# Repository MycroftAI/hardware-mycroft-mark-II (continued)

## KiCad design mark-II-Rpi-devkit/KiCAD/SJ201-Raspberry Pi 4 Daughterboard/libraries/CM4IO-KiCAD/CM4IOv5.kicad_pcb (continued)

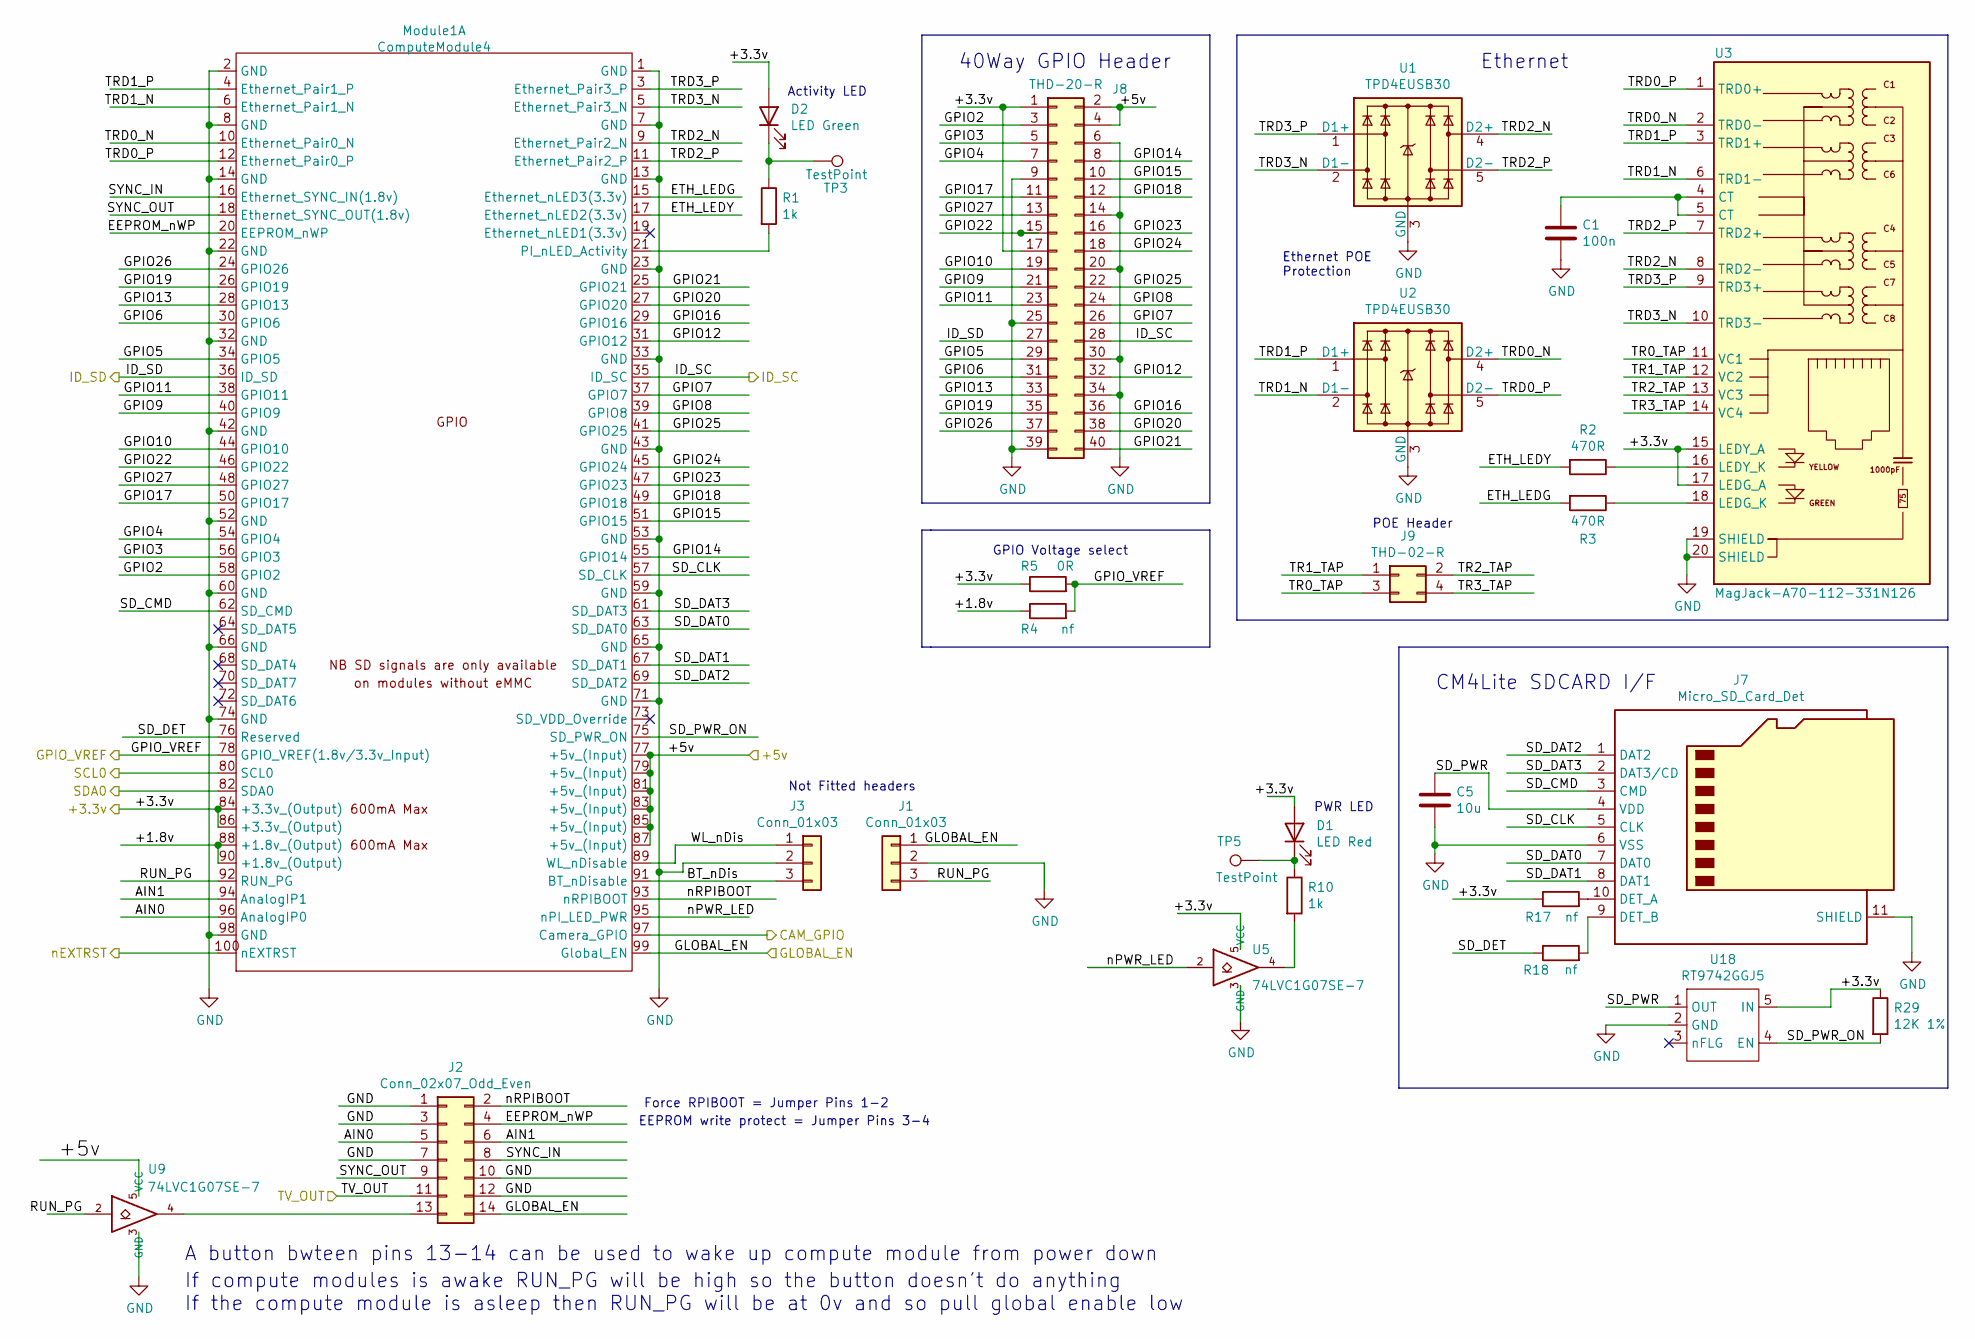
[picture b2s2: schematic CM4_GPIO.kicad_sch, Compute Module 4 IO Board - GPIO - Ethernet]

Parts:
C1: 100n; C_0402_1005Metric; Part Description 0.1uF 10% 16V Ceramic Capacitor X7R 040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
C5: 10u; C_0805_2012Metric; Part Description 10uF 10% 10V Ceramic Capacitor X7R 0805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
D1: LED Red; LED_0603_1608Metric; Part Description Red 620nm LED Indication - Discrete 2.2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
D2: LED Green; LED_0603_1608Metric; Part Description Green 572nm LED Indication - Discrete 2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
J1, J3: Conn_01x03; PinHeader_1x03_P2.54mm_Vertical; Part Description 3pin 0.1" connector
J2: Conn_02x07_Odd_Even; PinHeader_2x07_P2.54mm_Vertical; Part Description PinHeader_2x07_P2.54mm_Vertical
J7: Micro_SD_Card_Det; SDCARD_MOLEX_503398-1892; Part Description 9 (8 + 1) Position Card Connector micro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
J8: THD-20-R; PinHeader_2x20_P2.54mm_Vertical; Part Description PinHeader_2x20_P2.54mm_Vertical
J9: THD-02-R; PinHeader_2x02_P2.54mm_Vertical; Part Description PinHeader_2x02_P2.54mm_Vertical
Module1: ComputeModule4; Raspberry-Pi-4-Compute-Module; Part Description 100 Position Connector Receptacle, Cent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
R1, R10: 1k; R_0402_1005Metric; Part Description Resistor 1K M1005 1% 63mW
R2, R3: 470R; R_0402_1005Metric; Part Description Resistor 470R M1005 1% 63mW
R4: nf; R_0805_2012Metric_Pad1.15x1.40mm_HandSolder
R5: 0R; R_0805_2012Metric_Pad1.15x1.40mm_HandSolder; Part Description Resistor 0R M2012 5%
R17, R18: nf; R_0402_1005Metric; Part Description Resistor 1K M1005 1% 63mW
R29: 12K 1%; R_0402_1005Metric; Part Description Resistor 12K M1005 1% 63mW
TP3, TP5: TestPoint; TestPoint_Pad_2.0x2.0mm
U1, U2: TPD4EUSB30; USON-10_2.5x1.0mm_P0.5mm; Part Description Quad TVS diode for high speed signals (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
U3: MagJack-A70-112-331N126; TRJG0926HENL; Part Description Gigabit Ethernet Magjack
U5, U9: 74LVC1G07SE-7; SOT-353_SC-70-5; Part Description Buffer, Non-Inverting 1 Element 1 Bit p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
U18: RT9742GGJ5; SOT-23-5; Part Description Power Switch/Driver 1:1 N-Channel 1A TS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

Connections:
/+3.3v: D1.2 (A), D2.2 (A), J8.1, J8.17, Module1.84 (+3.3v_(Output)), Module1.86 (+3.3v_(Output)), R5.1, R17.1, R29.1, U3.15 (LEDY_A), U3.17 (LEDG_A), U5.5 (VCC), U18.5 (IN); also elsewhere on the board
/+5v: J8.2, J8.4, Module1.77 (+5v_(Input)), Module1.79 (+5v_(Input)), Module1.81 (+5v_(Input)), Module1.83 (+5v_(Input)), Module1.85 (+5v_(Input)), Module1.87 (+5v_(Input)), U9.5 (VCC); also elsewhere on the board
/CAM_GPIO: Module1.97 (Camera_GPIO); also elsewhere on the board
/CM4_GPIO ( Ethernet, GPIO, SDCARD)/+1.8v: Module1.88 (+1.8v_(Output)), Module1.90 (+1.8v_(Output)), R4.1
/CM4_GPIO ( Ethernet, GPIO, SDCARD)/AIN0: J2.5, Module1.96 (AnalogIP0)
/CM4_GPIO ( Ethernet, GPIO, SDCARD)/AIN1: J2.6, Module1.94 (AnalogIP1)
/CM4_GPIO ( Ethernet, GPIO, SDCARD)/BT_nDis: J3.3, Module1.91 (BT_nDisable)
/CM4_GPIO ( Ethernet, GPIO, SDCARD)/EEPROM_nWP: J2.4, Module1.20 (EEPROM_nWP)
/CM4_GPIO ( Ethernet, GPIO, SDCARD)/ETH_LEDG: Module1.15 (Ethernet_nLED3(3.3v)), R3.2
/CM4_GPIO ( Ethernet, GPIO, SDCARD)/ETH_LEDY: Module1.17 (Ethernet_nLED2(3.3v)), R2.2
/CM4_GPIO ( Ethernet, GPIO, SDCARD)/GPIO2: J8.3, Module1.58 (GPIO2)
/CM4_GPIO ( Ethernet, GPIO, SDCARD)/GPIO3: J8.5, Module1.56 (GPIO3)
/CM4_GPIO ( Ethernet, GPIO, SDCARD)/GPIO4: J8.7, Module1.54 (GPIO4)
/CM4_GPIO ( Ethernet, GPIO, SDCARD)/GPIO5: J8.29, Module1.34 (GPIO5)
/CM4_GPIO ( Ethernet, GPIO, SDCARD)/GPIO6: J8.31, Module1.30 (GPIO6)
/CM4_GPIO ( Ethernet, GPIO, SDCARD)/GPIO7: J8.26, Module1.37 (GPIO7)
/CM4_GPIO ( Ethernet, GPIO, SDCARD)/GPIO8: J8.24, Module1.39 (GPIO8)
/CM4_GPIO ( Ethernet, GPIO, SDCARD)/GPIO9: J8.21, Module1.40 (GPIO9)
/CM4_GPIO ( Ethernet, GPIO, SDCARD)/GPIO10: J8.19, Module1.44 (GPIO10)
/CM4_GPIO ( Ethernet, GPIO, SDCARD)/GPIO11: J8.23, Module1.38 (GPIO11)
/CM4_GPIO ( Ethernet, GPIO, SDCARD)/GPIO12: J8.32, Module1.31 (GPIO12)
/CM4_GPIO ( Ethernet, GPIO, SDCARD)/GPIO13: J8.33, Module1.28 (GPIO13)
/CM4_GPIO ( Ethernet, GPIO, SDCARD)/GPIO14: J8.8, Module1.55 (GPIO14)
/CM4_GPIO ( Ethernet, GPIO, SDCARD)/GPIO15: J8.10, Module1.51 (GPIO15)
/CM4_GPIO ( Ethernet, GPIO, SDCARD)/GPIO16: J8.36, Module1.29 (GPIO16)
/CM4_GPIO ( Ethernet, GPIO, SDCARD)/GPIO17: J8.11, Module1.50 (GPIO17)
/CM4_GPIO ( Ethernet, GPIO, SDCARD)/GPIO18: J8.12, Module1.49 (GPIO18)
/CM4_GPIO ( Ethernet, GPIO, SDCARD)/GPIO19: J8.35, Module1.26 (GPIO19)
/CM4_GPIO ( Ethernet, GPIO, SDCARD)/GPIO20: J8.38, Module1.27 (GPIO20)
/CM4_GPIO ( Ethernet, GPIO, SDCARD)/GPIO21: J8.40, Module1.25 (GPIO21)
/CM4_GPIO ( Ethernet, GPIO, SDCARD)/GPIO22: J8.15, Module1.46 (GPIO22)
/CM4_GPIO ( Ethernet, GPIO, SDCARD)/GPIO23: J8.16, Module1.47 (GPIO23)
/CM4_GPIO ( Ethernet, GPIO, SDCARD)/GPIO24: J8.18, Module1.45 (GPIO24)
/CM4_GPIO ( Ethernet, GPIO, SDCARD)/GPIO25: J8.22, Module1.41 (GPIO25)
/CM4_GPIO ( Ethernet, GPIO, SDCARD)/GPIO26: J8.37, Module1.24 (GPIO26)
/CM4_GPIO ( Ethernet, GPIO, SDCARD)/GPIO27: J8.13, Module1.48 (GPIO27)
/CM4_GPIO ( Ethernet, GPIO, SDCARD)/RUN_PG: J1.3, Module1.92 (RUN_PG), U9.2
/CM4_GPIO ( Ethernet, GPIO, SDCARD)/SD_CLK: J7.5 (CLK), Module1.57 (SD_CLK)
/CM4_GPIO ( Ethernet, GPIO, SDCARD)/SD_CMD: J7.3 (CMD), Module1.62 (SD_CMD)
/CM4_GPIO ( Ethernet, GPIO, SDCARD)/SD_DAT0: J7.7 (DAT0), Module1.63 (SD_DAT0)
/CM4_GPIO ( Ethernet, GPIO, SDCARD)/SD_DAT1: J7.8 (DAT1), Module1.67 (SD_DAT1)
/CM4_GPIO ( Ethernet, GPIO, SDCARD)/SD_DAT2: J7.1 (DAT2), Module1.69 (SD_DAT2)
/CM4_GPIO ( Ethernet, GPIO, SDCARD)/SD_DAT3: J7.2 (DAT3/CD), Module1.61 (SD_DAT3)
/CM4_GPIO ( Ethernet, GPIO, SDCARD)/SD_DET: Module1.76 (Reserved), R18.1
/CM4_GPIO ( Ethernet, GPIO, SDCARD)/SD_PWR: C5.1, J7.4 (VDD), U18.1 (OUT)
/CM4_GPIO ( Ethernet, GPIO, SDCARD)/SD_PWR_ON: Module1.75 (SD_PWR_ON), R29.2, U18.4 (EN)
/CM4_GPIO ( Ethernet, GPIO, SDCARD)/SYNC_IN: J2.8, Module1.16 (Ethernet_SYNC_IN(1.8v))
/CM4_GPIO ( Ethernet, GPIO, SDCARD)/SYNC_OUT: J2.9, Module1.18 (Ethernet_SYNC_OUT(1.8v))
/CM4_GPIO ( Ethernet, GPIO, SDCARD)/TR0_TAP: J9.3, U3.11 (VC1)
/CM4_GPIO ( Ethernet, GPIO, SDCARD)/TR1_TAP: J9.1, U3.12 (VC2)
/CM4_GPIO ( Ethernet, GPIO, SDCARD)/TR2_TAP: J9.2, U3.13 (VC3)
/CM4_GPIO ( Ethernet, GPIO, SDCARD)/TR3_TAP: J9.4, U3.14 (VC4)
/CM4_GPIO ( Ethernet, GPIO, SDCARD)/TRD0_N: Module1.10 (Ethernet_Pair0_N), U2.4 (D2+), U2.7, U3.2 (TRD0-)
/CM4_GPIO ( Ethernet, GPIO, SDCARD)/TRD0_P: Module1.12 (Ethernet_Pair0_P), U2.5 (D2-), U2.6, U3.1 (TRD0+)
/CM4_GPIO ( Ethernet, GPIO, SDCARD)/TRD1_N: Module1.6 (Ethernet_Pair1_N), U2.2 (D1-), U2.9, U3.6 (TRD1-)
/CM4_GPIO ( Ethernet, GPIO, SDCARD)/TRD1_P: Module1.4 (Ethernet_Pair1_P), U2.1 (D1+), U2.10, U3.3 (TRD1+)
/CM4_GPIO ( Ethernet, GPIO, SDCARD)/TRD2_N: Module1.9 (Ethernet_Pair2_N), U1.4 (D2+), U1.7, U3.8 (TRD2-)
/CM4_GPIO ( Ethernet, GPIO, SDCARD)/TRD2_P: Module1.11 (Ethernet_Pair2_P), U1.5 (D2-), U1.6, U3.7 (TRD2+)
/CM4_GPIO ( Ethernet, GPIO, SDCARD)/TRD3_N: Module1.5 (Ethernet_Pair3_N), U1.2 (D1-), U1.9, U3.10 (TRD3-)
/CM4_GPIO ( Ethernet, GPIO, SDCARD)/TRD3_P: Module1.3 (Ethernet_Pair3_P), U1.1 (D1+), U1.10, U3.9 (TRD3+)
/CM4_GPIO ( Ethernet, GPIO, SDCARD)/WL_nDis: J3.1, Module1.89 (WL_nDisable)
/CM4_GPIO ( Ethernet, GPIO, SDCARD)/nPWR_LED: Module1.95 (nPI_LED_PWR), U5.2
/CM4_GPIO ( Ethernet, GPIO, SDCARD)/nRPIBOOT: J2.2, Module1.93 (nRPIBOOT)
/GLOBAL_EN: J1.1, J2.14, Module1.99 (Global_EN); also elsewhere on the board
/GPIO_VREF: Module1.78 (GPIO_VREF(1.8v/3.3v_Input)), R4.2, R5.2; also elsewhere on the board
/ID_SC: J8.28, Module1.35 (ID_SC); also elsewhere on the board
/ID_SD: J8.27, Module1.36 (ID_SD); also elsewhere on the board
/SCL0: Module1.80 (SCL0); also elsewhere on the board
/SDA0: Module1.82 (SDA0); also elsewhere on the board
/TV_OUT: J2.11; also elsewhere on the board
/nEXTRST: Module1.100 (nEXTRST); also elsewhere on the board
GND: C1.2, C5.2, J1.2, J2.1, J2.3, J2.7, J2.10, J2.12, J3.2, J7.6 (VSS), J7.11 (SHIELD), J8.6, J8.9, J8.14, J8.20, J8.25, J8.30, J8.34, J8.39, Module1.1 (GND), Module1.2 (GND), Module1.7 (GND), Module1.8 (GND), Module1.13 (GND), Module1.14 (GND), Module1.22 (GND), Module1.23 (GND), Module1.32 (GND), Module1.33 (GND), Module1.42 (GND), Module1.43 (GND), Module1.52 (GND), Module1.53 (GND), Module1.59 (GND), Module1.60 (GND), Module1.65 (GND), Module1.66 (GND), Module1.71 (GND), Module1.74 (GND), Module1.98 (GND), U1.3 (GND), U1.8 (GND), U2.3 (GND), U2.8 (GND), U3.19 (SHIELD), U3.20 (SHIELD), U5.3 (GND), U9.3 (GND), U18.2 (GND); also elsewhere on the board
unnamed: C1.1, U3.4 (CT), U3.5 (CT)
unnamed: D1.1 (K), R10.1, TP5.1
unnamed: D2.1 (K), R1.1, TP3.1
unnamed: J2.13, U9.4
unnamed: J7.9 (DET_B), R18.2
unnamed: J7.10 (DET_A), R17.2
unnamed: Module1.21 (PI_nLED_Activity), R1.2
unnamed: R2.1, U3.16 (LEDY_K)
unnamed: R3.1, U3.18 (LEDG_K)
unnamed: R10.2, U5.4

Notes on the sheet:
A button bwteen pins 13-14 can be used to wake up compute module from power down
If compute modules is awake RUN_PG will be high so the button doesn't do anything If the compute module is asleep then RUN_PG will be at 0v and so pull global enable low
Activity LED
Force RPIBOOT = Jumper Pins 1-2
Not Fitted headers
EEPROM write protect = Jumper Pins 3-4
40Way GPIO Header
GPIO Voltage select
Ethernet POE Protection
PWR LED
POE Header
CM4Lite SDCARD I/F
Ethernet

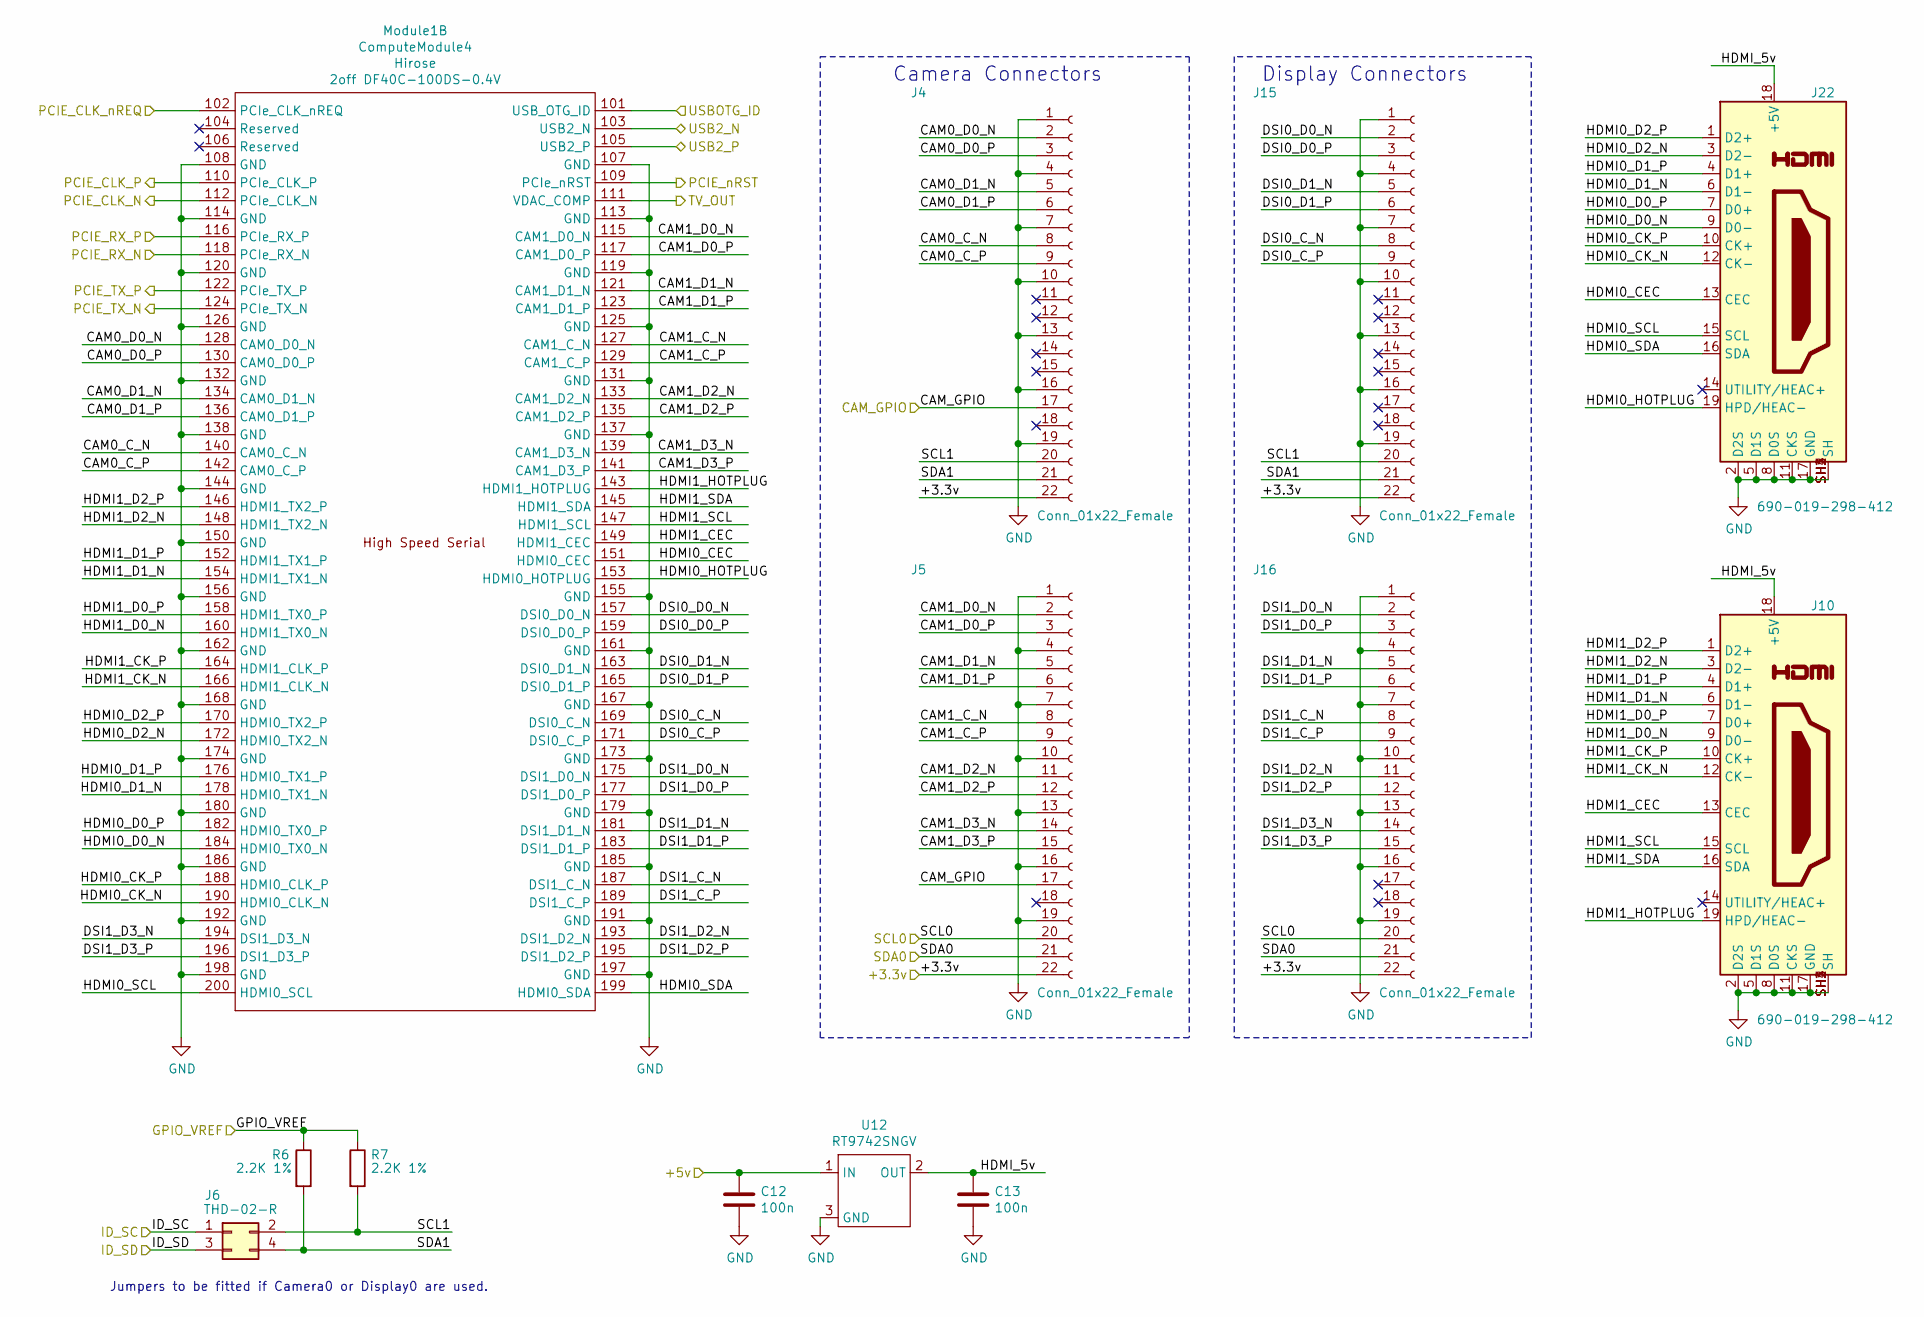
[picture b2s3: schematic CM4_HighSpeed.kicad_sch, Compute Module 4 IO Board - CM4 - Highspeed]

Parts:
C12, C13: 100n; C_0402_1005Metric; Part Description 0.1uF 10% 16V Ceramic Capacitor X7R 040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
J4, J5, J15, J16: Conn_01x22_Female; Hirose_FH12-22S-0.5SH_1x22-1MP_P0.50mm_Horizontal; Part Description 22 Position FFC, FPC Connector Contacts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
J6: THD-02-R; PinHeader_2x02_P2.54mm_Vertical; Part Description PinHeader_2x02_P2.54mm_Vertical
J10, J22: 690-019-298-412; EDAC 690-019-298-412; Part Description HDMI Connector, Right Angle, 19 Contact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
Module1: ComputeModule4; Raspberry-Pi-4-Compute-Module; Part Description 100 Position Connector Receptacle, Cent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
R6, R7: 2.2K 1%; R_0402_1005Metric; Part Description Resistor 2.2K M1005 1% 63mW
U12: RT9742SNGV; SOT-23; Part Description Power Switch/Driver 1:1 N-Channel 500mA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

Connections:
/+3.3v: J4.22, J5.22, J15.22, J16.22; also elsewhere on the board
/+5v: C12.1, U12.1 (IN); also elsewhere on the board
/CAM_GPIO: J4.17, J5.17; also elsewhere on the board
/CM4_HighSpeed/CAM0_C_N: J4.8, Module1.140 (CAM0_C_N)
/CM4_HighSpeed/CAM0_C_P: J4.9, Module1.142 (CAM0_C_P)
/CM4_HighSpeed/CAM0_D0_N: J4.2, Module1.128 (CAM0_D0_N)
/CM4_HighSpeed/CAM0_D0_P: J4.3, Module1.130 (CAM0_D0_P)
/CM4_HighSpeed/CAM0_D1_N: J4.5, Module1.134 (CAM0_D1_N)
/CM4_HighSpeed/CAM0_D1_P: J4.6, Module1.136 (CAM0_D1_P)
/CM4_HighSpeed/CAM1_C_N: J5.8, Module1.127 (CAM1_C_N)
/CM4_HighSpeed/CAM1_C_P: J5.9, Module1.129 (CAM1_C_P)
/CM4_HighSpeed/CAM1_D0_N: J5.2, Module1.115 (CAM1_D0_N)
/CM4_HighSpeed/CAM1_D0_P: J5.3, Module1.117 (CAM1_D0_P)
/CM4_HighSpeed/CAM1_D1_N: J5.5, Module1.121 (CAM1_D1_N)
/CM4_HighSpeed/CAM1_D1_P: J5.6, Module1.123 (CAM1_D1_P)
/CM4_HighSpeed/CAM1_D2_N: J5.11, Module1.133 (CAM1_D2_N)
/CM4_HighSpeed/CAM1_D2_P: J5.12, Module1.135 (CAM1_D2_P)
/CM4_HighSpeed/CAM1_D3_N: J5.14, Module1.139 (CAM1_D3_N)
/CM4_HighSpeed/CAM1_D3_P: J5.15, Module1.141 (CAM1_D3_P)
/CM4_HighSpeed/DSI0_C_N: J15.8, Module1.169 (DSI0_C_N)
/CM4_HighSpeed/DSI0_C_P: J15.9, Module1.171 (DSI0_C_P)
/CM4_HighSpeed/DSI0_D0_N: J15.2, Module1.157 (DSI0_D0_N)
/CM4_HighSpeed/DSI0_D0_P: J15.3, Module1.159 (DSI0_D0_P)
/CM4_HighSpeed/DSI0_D1_N: J15.5, Module1.163 (DSI0_D1_N)
/CM4_HighSpeed/DSI0_D1_P: J15.6, Module1.165 (DSI0_D1_P)
/CM4_HighSpeed/DSI1_C_N: J16.8, Module1.187 (DSI1_C_N)
/CM4_HighSpeed/DSI1_C_P: J16.9, Module1.189 (DSI1_C_P)
/CM4_HighSpeed/DSI1_D0_N: J16.2, Module1.175 (DSI1_D0_N)
/CM4_HighSpeed/DSI1_D0_P: J16.3, Module1.177 (DSI1_D0_P)
/CM4_HighSpeed/DSI1_D1_N: J16.5, Module1.181 (DSI1_D1_N)
/CM4_HighSpeed/DSI1_D1_P: J16.6, Module1.183 (DSI1_D1_P)
/CM4_HighSpeed/DSI1_D2_N: J16.11, Module1.193 (DSI1_D2_N)
/CM4_HighSpeed/DSI1_D2_P: J16.12, Module1.195 (DSI1_D2_P)
/CM4_HighSpeed/DSI1_D3_N: J16.14, Module1.194 (DSI1_D3_N)
/CM4_HighSpeed/DSI1_D3_P: J16.15, Module1.196 (DSI1_D3_P)
/CM4_HighSpeed/HDMI0_CEC: J22.13 (CEC), Module1.151 (HDMI0_CEC)
/CM4_HighSpeed/HDMI0_CK_N: J22.12 (CK-), Module1.190 (HDMI0_CLK_N)
/CM4_HighSpeed/HDMI0_CK_P: J22.10 (CK+), Module1.188 (HDMI0_CLK_P)
/CM4_HighSpeed/HDMI0_D0_N: J22.9 (D0-), Module1.184 (HDMI0_TX0_N)
/CM4_HighSpeed/HDMI0_D0_P: J22.7 (D0+), Module1.182 (HDMI0_TX0_P)
/CM4_HighSpeed/HDMI0_D1_N: J22.6 (D1-), Module1.178 (HDMI0_TX1_N)
/CM4_HighSpeed/HDMI0_D1_P: J22.4 (D1+), Module1.176 (HDMI0_TX1_P)
/CM4_HighSpeed/HDMI0_D2_N: J22.3 (D2-), Module1.172 (HDMI0_TX2_N)
/CM4_HighSpeed/HDMI0_D2_P: J22.1 (D2+), Module1.170 (HDMI0_TX2_P)
/CM4_HighSpeed/HDMI0_HOTPLUG: J22.19 (HPD/HEAC-), Module1.153 (HDMI0_HOTPLUG)
/CM4_HighSpeed/HDMI0_SCL: J22.15 (SCL), Module1.200 (HDMI0_SCL)
/CM4_HighSpeed/HDMI0_SDA: J22.16 (SDA), Module1.199 (HDMI0_SDA)
/CM4_HighSpeed/HDMI1_CEC: J10.13 (CEC), Module1.149 (HDMI1_CEC)
/CM4_HighSpeed/HDMI1_CK_N: J10.12 (CK-), Module1.166 (HDMI1_CLK_N)
/CM4_HighSpeed/HDMI1_CK_P: J10.10 (CK+), Module1.164 (HDMI1_CLK_P)
/CM4_HighSpeed/HDMI1_D0_N: J10.9 (D0-), Module1.160 (HDMI1_TX0_N)
/CM4_HighSpeed/HDMI1_D0_P: J10.7 (D0+), Module1.158 (HDMI1_TX0_P)
/CM4_HighSpeed/HDMI1_D1_N: J10.6 (D1-), Module1.154 (HDMI1_TX1_N)
/CM4_HighSpeed/HDMI1_D1_P: J10.4 (D1+), Module1.152 (HDMI1_TX1_P)
/CM4_HighSpeed/HDMI1_D2_N: J10.3 (D2-), Module1.148 (HDMI1_TX2_N)
/CM4_HighSpeed/HDMI1_D2_P: J10.1 (D2+), Module1.146 (HDMI1_TX2_P)
/CM4_HighSpeed/HDMI1_HOTPLUG: J10.19 (HPD/HEAC-), Module1.143 (HDMI1_HOTPLUG)
/CM4_HighSpeed/HDMI1_SCL: J10.15 (SCL), Module1.147 (HDMI1_SCL)
/CM4_HighSpeed/HDMI1_SDA: J10.16 (SDA), Module1.145 (HDMI1_SDA)
/CM4_HighSpeed/HDMI_5v: C13.1, J10.18 (+5V), J22.18 (+5V), U12.2 (OUT)
/CM4_HighSpeed/SCL1: J4.20, J6.2, J15.20, R7.2
/CM4_HighSpeed/SDA1: J4.21, J6.4, J15.21, R6.2
/GPIO_VREF: R6.1, R7.1; also elsewhere on the board
/ID_SC: J6.1; also elsewhere on the board
/ID_SD: J6.3; also elsewhere on the board
/PCIE_CLK_N: Module1.112 (PCIe_CLK_N); also elsewhere on the board
/PCIE_CLK_P: Module1.110 (PCIe_CLK_P); also elsewhere on the board
/PCIE_CLK_nREQ: Module1.102 (PCIe_CLK_nREQ); also elsewhere on the board
/PCIE_RX_N: Module1.118 (PCIe_RX_N); also elsewhere on the board
/PCIE_RX_P: Module1.116 (PCIe_RX_P); also elsewhere on the board
/PCIE_TX_N: Module1.124 (PCIe_TX_N); also elsewhere on the board
/PCIE_TX_P: Module1.122 (PCIe_TX_P); also elsewhere on the board
/PCIE_nRST: Module1.109 (PCIe_nRST); also elsewhere on the board
/SCL0: J5.20, J16.20; also elsewhere on the board
/SDA0: J5.21, J16.21; also elsewhere on the board
/TV_OUT: Module1.111 (VDAC_COMP); also elsewhere on the board
/USB2_N: Module1.103 (USB2_N); also elsewhere on the board
/USB2_P: Module1.105 (USB2_P); also elsewhere on the board
/USBOTG: Module1.101 (USB_OTG_ID); also elsewhere on the board
GND: C12.2, C13.2, J4.1, J4.4, J4.7, J4.10, J4.13, J4.16, J4.19, J5.1, J5.4, J5.7, J5.10, J5.13, J5.16, J5.19, J10.2 (D2S), J10.5 (D1S), J10.8 (D0S), J10.11 (CKS), J10.17 (GND), J10.SH1 (SH), J10.SH2 (SH), J10.SH3 (SH), J10.SH4 (SH), J15.1, J15.4, J15.7, J15.10, J15.13, J15.16, J15.19, J16.1, J16.4, J16.7, J16.10, J16.13, J16.16, J16.19, J22.2 (D2S), J22.5 (D1S), J22.8 (D0S), J22.11 (CKS), J22.17 (GND), J22.SH1 (SH), J22.SH2 (SH), J22.SH3 (SH), J22.SH4 (SH), Module1.107 (GND), Module1.108 (GND), Module1.113 (GND), Module1.114 (GND), Module1.119 (GND), Module1.120 (GND), Module1.125 (GND), Module1.126 (GND), Module1.131 (GND), Module1.132 (GND), Module1.137 (GND), Module1.138 (GND), Module1.144 (GND), Module1.150 (GND), Module1.155 (GND), Module1.156 (GND), Module1.161 (GND), Module1.162 (GND), Module1.167 (GND), Module1.168 (GND), Module1.173 (GND), Module1.174 (GND), Module1.179 (GND), Module1.180 (GND), Module1.185 (GND), Module1.186 (GND), Module1.191 (GND), Module1.192 (GND), Module1.197 (GND), Module1.198 (GND), U12.3 (GND); also elsewhere on the board

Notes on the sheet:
Jumpers to be fitted if Camera0 or Display0 are used.
Camera Connectors
Display Connectors

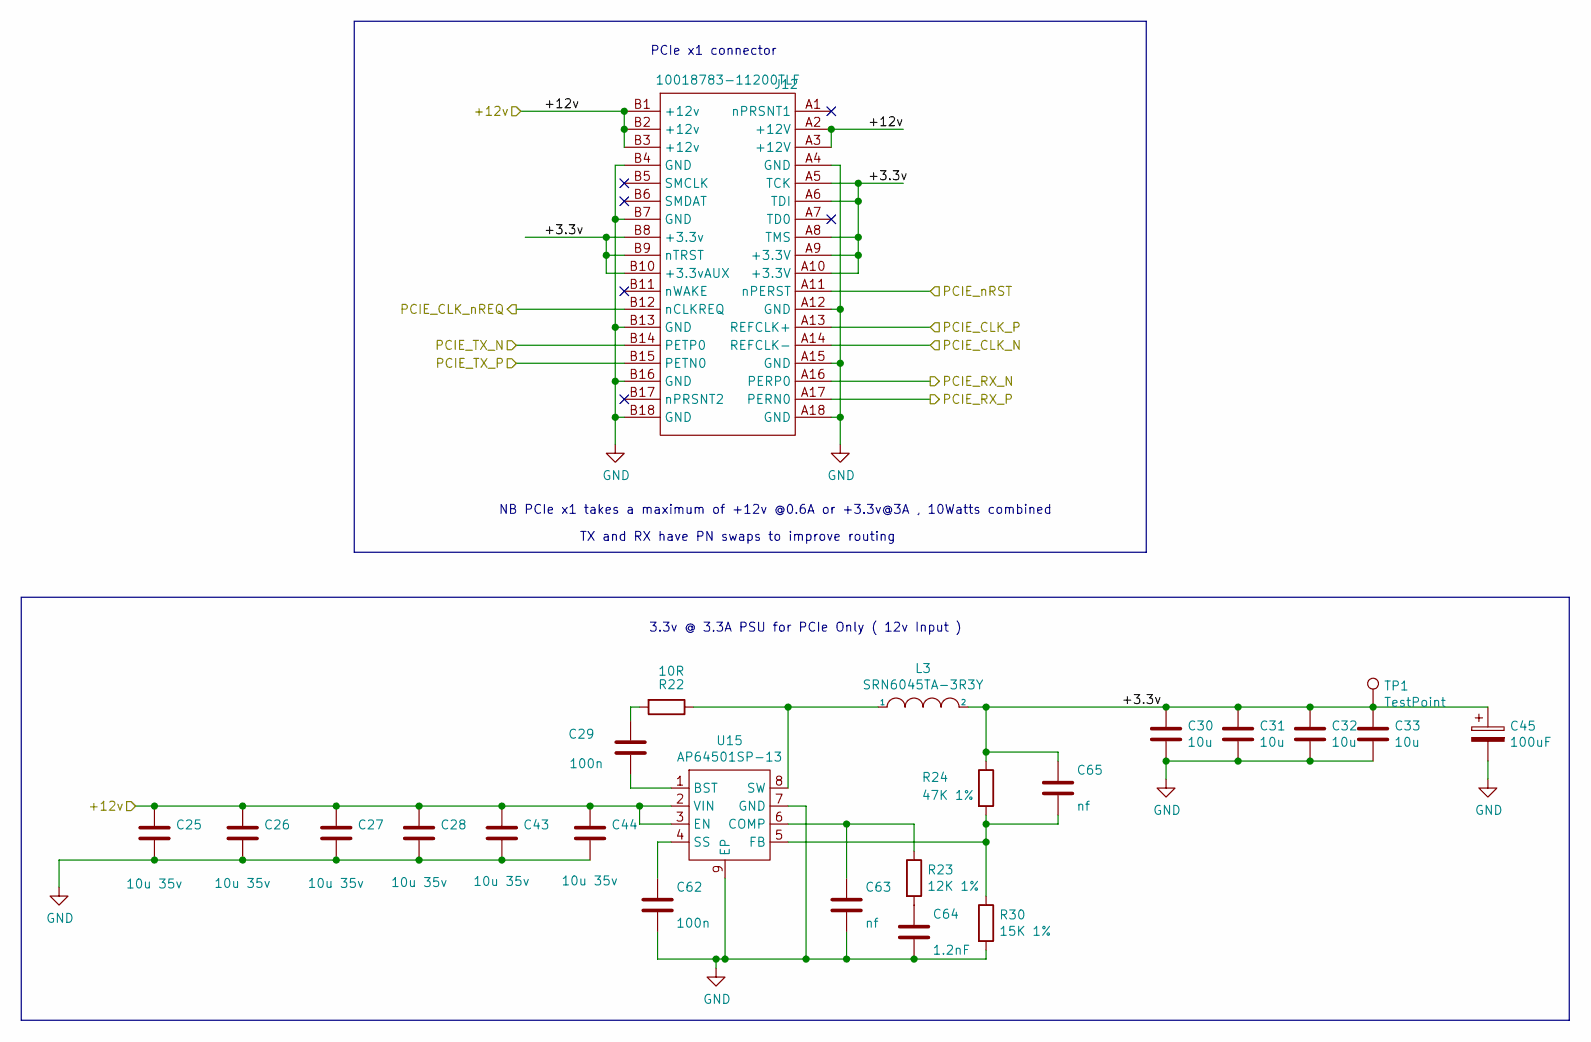
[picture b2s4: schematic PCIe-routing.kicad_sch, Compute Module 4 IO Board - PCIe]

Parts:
C25, C26, C27, C28, C43, C44: 10u 35v; C_0805_2012Metric; Part Description 10uF 10% or 20% 35V Ceramic Capacitor X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
C29, C62: 100n; C_0402_1005Metric; Part Description 0.1uF 10% 16V Ceramic Capacitor X7R 040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
C30, C31, C32, C33: 10u; C_0805_2012Metric; Part Description 10uF 10% 10V Ceramic Capacitor X7R 0805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
C45: 100uF; CP_EIA-7343-31_Kemet-D; Part Description Capacitor, SP-Cap, 100u, 6.3V, 15mR ESR
C63: nf; C_0402_1005Metric
C64: 1.2nF; C_0402_1005Metric; Part Description 1200pF 10% 10V Ceramic Capacitor X5R 04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
C65: nf; C_0402_1005Metric; Part Description 27pF 5% 50V Ceramic Capacitor C0G, NP0 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
J12: 10018783-11200TLF; PCIex1-36; Part Description PCI Express/PCI Connectors PCIE THROUGH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
L3: SRN6045TA-3R3Y; L_Bourns_SRN6045TA; Part Description 3.3µH Semi-Shielded Wirewound Inductor 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
R22: 10R; R_0402_1005Metric; Part Description Resistor 10R M1005 1% 63mW
R23: 12K 1%; R_0402_1005Metric; Part Description Resistor 12K M1005 1% 63mW
R24: 47K 1%; R_0402_1005Metric; Part Description Resistor 47K M1005 1% 63mW
R30: 15K 1%; R_0402_1005Metric; Part Description Resistor 15K M1005 1% 63mW
TP1: TestPoint; TestPoint_Pad_2.0x2.0mm
U15: AP64501SP-13; SOIC-8-1EP_3.9x4.9mm_P1.27mm_EP2.95x4.9mm_Mask2.71x3.4mm_Th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; Part Description Buck Switching Regulator IC Positive Ad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

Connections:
/+12v: C25.1, C26.1, C27.1, C28.1, C43.1, C44.1, J12.A2 (+12V), J12.A3 (+12V), J12.B1 (+12v), J12.B2 (+12v), J12.B3 (+12v), U15.2 (VIN), U15.3 (EN); also elsewhere on the board
/PCIE_CLK_N: J12.A14 (REFCLK-); also elsewhere on the board
/PCIE_CLK_P: J12.A13 (REFCLK+); also elsewhere on the board
/PCIE_CLK_nREQ: J12.B12 (nCLKREQ); also elsewhere on the board
/PCIE_RX_N: J12.A16 (PERP0); also elsewhere on the board
/PCIE_RX_P: J12.A17 (PERN0); also elsewhere on the board
/PCIE_TX_N: J12.B14 (PETP0); also elsewhere on the board
/PCIE_TX_P: J12.B15 (PETN0); also elsewhere on the board
/PCIE_nRST: J12.A11 (nPERST); also elsewhere on the board
/PCIe-connector/+3.3v: C30.1, C31.1, C32.1, C33.1, C45.1, C65.1, J12.A5 (TCK), J12.A6 (TDI), J12.A8 (TMS), J12.A9 (+3.3V), J12.A10 (+3.3V), J12.B8 (+3.3v), J12.B9 (nTRST), J12.B10 (+3.3vAUX), L3.2, R24.1, TP1.1
GND: C25.2, C26.2, C27.2, C28.2, C30.2, C31.2, C32.2, C33.2, C43.2, C44.2, C45.2, C62.2, C63.2, C64.2, J12.A4 (GND), J12.A12 (GND), J12.A15 (GND), J12.A18 (GND), J12.B4 (GND), J12.B7 (GND), J12.B13 (GND), J12.B16 (GND), J12.B18 (GND), R30.2, U15.7 (GND), U15.9 (EP); also elsewhere on the board
unnamed: C29.1, R22.2
unnamed: C29.2, U15.1 (BST)
unnamed: C62.1, U15.4 (SS)
unnamed: C63.1, R23.1, U15.6 (COMP)
unnamed: C64.1, R23.2
unnamed: C65.2, R24.2, R30.1, U15.5 (FB)
unnamed: L3.1, R22.1, U15.8 (SW)

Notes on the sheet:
NB PCIe x1 takes a maximum of +12v @0.6A or +3.3v@3A , 10Watts combined
TX and RX have PN swaps to improve routing
3.3v @ 3.3A PSU for PCIe Only ( 12v Input )
PCIe x1 connector

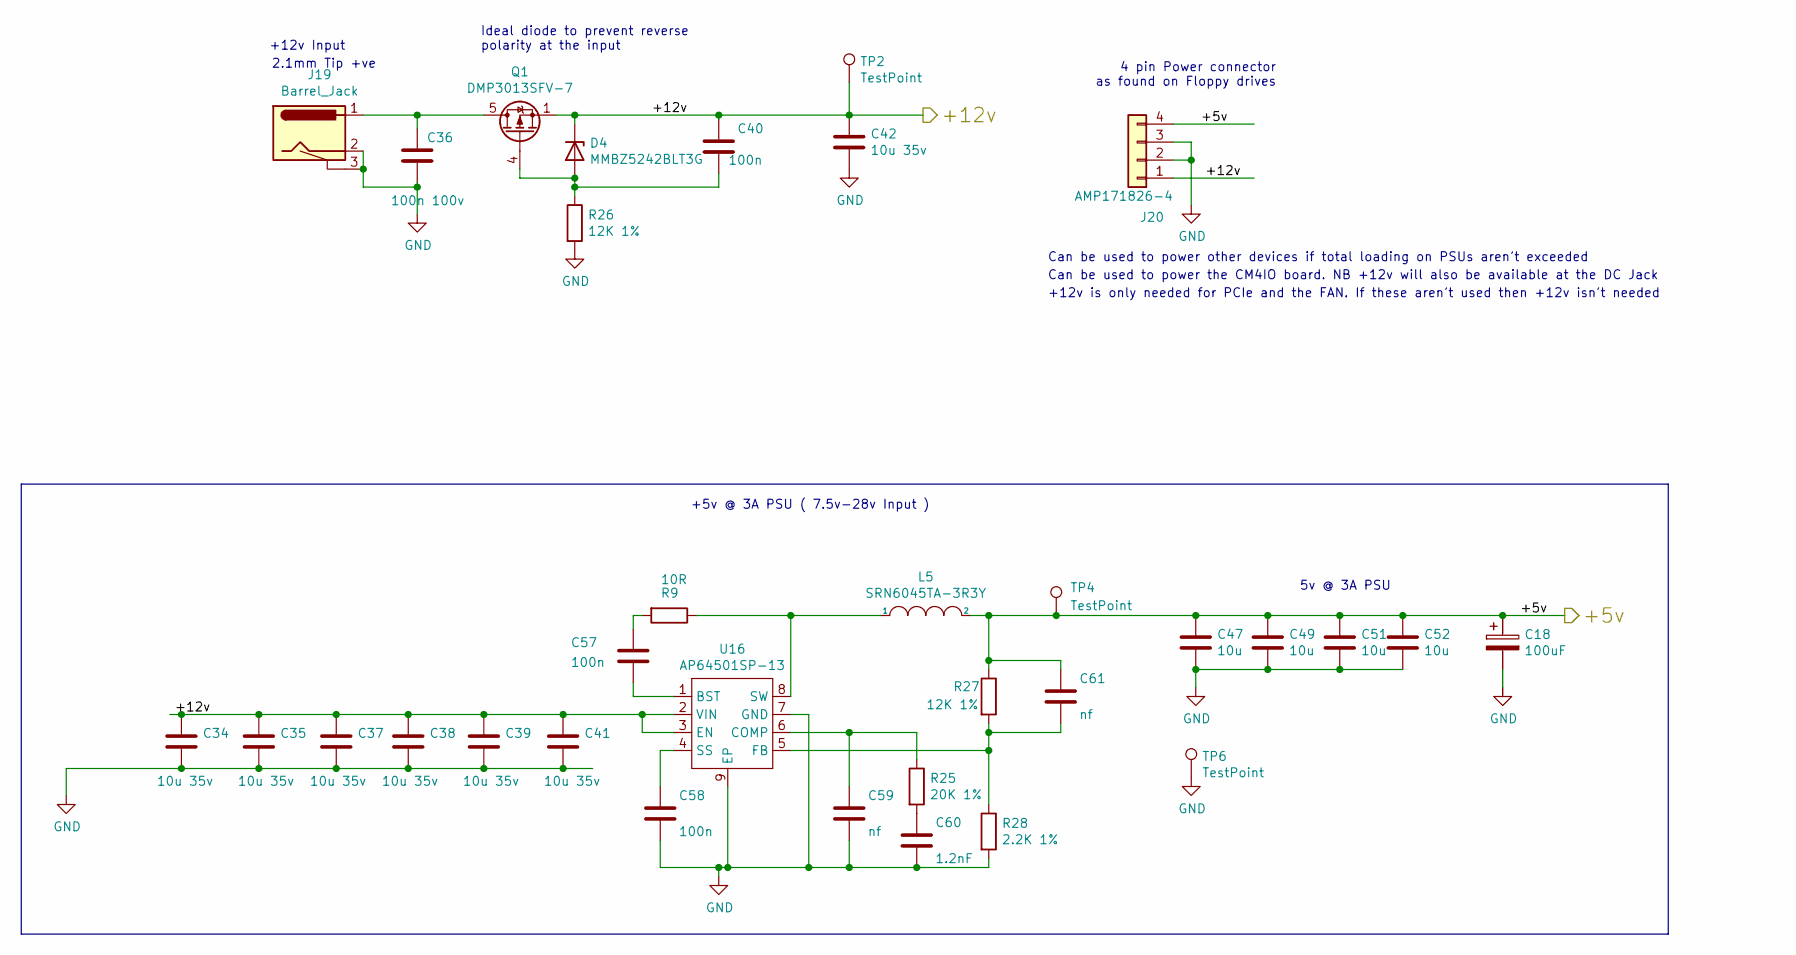
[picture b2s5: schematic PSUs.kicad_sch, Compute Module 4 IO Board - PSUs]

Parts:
C18: 100uF; CP_EIA-7343-31_Kemet-D; Part Description Capacitor, SP-Cap, 100u, 6.3V, 15mR ESR
C34, C35, C37, C38, C39, C41, C42: 10u 35v; C_0805_2012Metric; Part Description 10uF 10% or 20% 35V Ceramic Capacitor X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
C36: 100n 100v; C_0402_1005Metric; Part Description 0.1uF 10% 100V Ceramic Capacitor X5R 04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
C40, C57, C58: 100n; C_0402_1005Metric; Part Description 0.1uF 10% 16V Ceramic Capacitor X7R 040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
C47, C49, C51, C52: 10u; C_0805_2012Metric; Part Description 10uF 10% 10V Ceramic Capacitor X7R 0805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
C59: nf; C_0402_1005Metric
C60: 1.2nF; C_0402_1005Metric; Part Description 1200pF 10% 10V Ceramic Capacitor X5R 04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
C61: nf; C_0402_1005Metric; Part Description 220 pF, 50 V, 0402 [1005 Metric], ± 5%,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
D4: MMBZ5242BLT3G; D_SOT-23_ANK; Part Description Zener Diode 12V 225mW 5% Surface Mount 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
J19: Barrel_Jack; BarrelJack_Horizontal; Part Description DC Power Connectors PCB 2.1MM
J20: AMP171826-4; TE_171826-4; Part Description Wire-To-Board Connector, Right Angle, 2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
L5: SRN6045TA-3R3Y; L_Bourns_SRN6045TA; Part Description 3.3µH Semi-Shielded Wirewound Inductor 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
Q1: DMP3013SFV-7; Diodes_PowerDI3333-8; Part Description DMP3013SFV-7 - Power MOSFET, P Channel,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
R9: 10R; R_0402_1005Metric; Part Description Resistor 10R M1005 1% 63mW
R25: 20K 1%; R_0402_1005Metric; Part Description Resistor 20K M1005 1% 63mW
R26, R27: 12K 1%; R_0402_1005Metric; Part Description Resistor 12K M1005 1% 63mW
R28: 2.2K 1%; R_0402_1005Metric; Part Description Resistor 2.2K M1005 1% 63mW
TP2, TP4, TP6: TestPoint; TestPoint_Pad_2.0x2.0mm
U16: AP64501SP-13; SOIC-8-1EP_3.9x4.9mm_P1.27mm_EP2.95x4.9mm_Mask2.71x3.4mm_Th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; Part Description Buck Switching Regulator IC Positive Ad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

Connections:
/+5v: C18.1, C47.1, C49.1, C51.1, C52.1, C61.1, J20.4, L5.2, R27.1, TP4.1; also elsewhere on the board
/+12v: C34.1, C35.1, C37.1, C38.1, C39.1, C40.1, C41.1, C42.1, D4.1 (K), J20.1, Q1.1 (S), Q1.2 (S), Q1.3 (S), TP2.1, U16.2 (VIN), U16.3 (EN); also elsewhere on the board
GND: C18.2, C34.2, C35.2, C36.2, C37.2, C38.2, C39.2, C41.2, C42.2, C47.2, C49.2, C51.2, C52.2, C58.2, C59.2, C60.2, J19.2, J19.3, J20.2, J20.3, R26.2, R28.2, TP6.1, U16.7 (GND), U16.9 (EP); also elsewhere on the board
unnamed: C36.1, J19.1, Q1.5 (D)
unnamed: C40.2, D4.2 (A), Q1.4 (G), R26.1
unnamed: C57.1, R9.2
unnamed: C57.2, U16.1 (BST)
unnamed: C58.1, U16.4 (SS)
unnamed: C59.1, R25.1, U16.6 (COMP)
unnamed: C60.1, R25.2
unnamed: C61.2, R27.2, R28.1, U16.5 (FB)
unnamed: L5.1, R9.1, U16.8 (SW)

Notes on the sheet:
+12v Input
2.1mm Tip +ve
Ideal diode to prevent reverse polarity at the input
+5v @ 3A PSU ( 7.5v-28v Input )
Can be used to power other devices if total loading on PSUs aren't exceeded
Can be used to power the CM4IO board. NB +12v will also be available at the DC Jack
+12v is only needed for PCIe and the FAN. If these aren't used then +12v isn't needed
4 pin Power connector as found on Floppy drives
5v @ 3A PSU
